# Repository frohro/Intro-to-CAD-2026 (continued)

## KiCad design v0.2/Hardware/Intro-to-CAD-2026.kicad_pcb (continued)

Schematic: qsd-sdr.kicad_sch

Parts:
C1, C20, C23, C30, C31, C32, C52, C81: 100nF; C_0805; Voltage Rated 100V; Tolerance ±10%; Part CL21B104KCFNNNE; LCSC C28233
C14, C16, C19, C22: 10nF; C_0603; Voltage Rated 50V; Tolerance ±5%; LCSC C1664
C18, C28, C93, C94: 330pF; C_0603; Voltage Rated 50V; Tolerance ±5%; Part CL10C331JB8NNNC; LCSC C1664
C21, C29: 1uF; C_0805; Voltage Rated 50V; Tolerance ±10%; Part CL21B105KBFNNNE; LCSC C28323
C33: 10uF; C_1206; Voltage Rated 50V; Tolerance ±10%; Part CL31A106KBHNNNE; LCSC C13585
C82, C83: 100uF; C_CASE-B-3528-21(mm); Tolerance ±10%; Rated Voltage 6.3V; Part TAJB107K006RNJ; LCSC C16133
FB3: FB_0805; Current Rating 500mA; Tolerance ±25%; Part GZ2012D601TF; LCSC C1017
J11: SDR ANT; Conn_Coaxial_Frohne; not fitted
J12: SDR Out; Jack_3.5mm_CUI_SJ-3523-SMT_Horizontal; LCSC C18594
JP1: Turns; SolderJumper-2_P1.3mm_Bridged2Bar_RoundedPad1.0x1.5mm
JP9, JP10: 330pf; SolderJumper-2_P1.3mm_Bridged_RoundedPad1.0x1.5mm
JP86: Filter; SolderJumper-2_P1.3mm_Bridged2Bar_RoundedPad1.0x1.5mm
JP88, JP89: GND_LP_SND; SolderJumper-2_P1.3mm_Open_RoundedPad1.0x1.5mm
Je3: Filter; PinHeader_1x04_P2.54mm_Vertical; LCSC C2718488; not fitted
R1, R4: 10kΩ; R_0805; Overload Voltage (Max) 150V; Tolerance ±1%; Part 0805W8F1002T5E; LCSC C17414
R8, R9: 47Ω; R_0805; Overload Voltage (Max) 150V; Tolerance ±1%; Part 0805W8F470JT5E; LCSC C17714
R11: 1Ω; R_0805; Overload Voltage (Max) 150V; Tolerance ±1%; Part 0805W8F100KT5E; LCSC C25271
R12, R13: 1.5kΩ; R_0402; Overload Voltage (Max) 50V; Tolerance ±1%; Part 0402WGF1501TCE; LCSC C25867
R30: 10Ω; R_0603; Overload Voltage (Max) 75V; Tolerance ±1%; Part 0603WAF100JT5E; LCSC C22859
R58, R59, R60, R61: 10Ω; R_0402; Overload Voltage (Max) 50V; Tolerance ±1%; Part 0402WGF100JTCE; LCSC C25077
TP6: 180; TestPoint_THTPad_D2.0mm_Drill1.0mm
TP7: 270; TestPoint_THTPad_D2.0mm_Drill1.0mm
TP10, TP12: GND; TestPoint_THTPad_D2.0mm_Drill1.0mm
TP11: VA/2; TestPoint_THTPad_D2.0mm_Drill1.0mm
TP14: 0; TestPoint_THTPad_D2.0mm_Drill1.0mm
TP16: 90; TestPoint_THTPad_D2.0mm_Drill1.0mm
TP17: I; TestPoint_THTPad_D2.0mm_Drill1.0mm
TP18: Q; TestPoint_THTPad_D2.0mm_Drill1.0mm
TR1: H1102NLT; XFMR_H1102NLT; LCSC C20623173
U5, U8: OPA1612AxD; SOIC-8_3.9x4.9mm_P1.27mm; LCSC C94590
U7: SN74CBT3253DBQR; DBQ0016A-IPC_A; LCSC C2674552
e5: Groundloop_Insurance; SolderJumper-2_P1.3mm_Bridged_RoundedPad1.0x1.5mm

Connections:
/I: C29.2, J12.R; also elsewhere on the board
/I_CLK: U7.14 (S0); also elsewhere on the board
/Q: C21.1, J12.T; also elsewhere on the board
/Q_CLK: U7.2 (S1); also elsewhere on the board
GND: C14.2, C16.2, C19.2, C20.1, C22.2, C23.1, C30.1, C31.1, C32.1, C33.2, C52.1, C82.2, JP89.1 (A), R4.1, R30.2, TP10.1 (1_1), TP12.1 (1_1), U5.4 (V-), U7.1 (1~OE), U7.8 (GND), U7.15 (2~OE), U8.4 (V-), e5.1 (A); also elsewhere on the board
unnamed: C33.1, R11.2
unnamed: J11.2 (Ext), JP1.1 (A), JP88.1 (A), JP89.2 (B), Je3.2, Je3.3
unnamed: C1.1, J11.1 (In)
unnamed: JP1.2 (B), TR1.7 (C_RD)
unnamed: C18.2, C29.1, JP9.1 (A), R12.2, TP17.1 (1_1), U8.7
unnamed: C93.2, JP9.2 (B)
unnamed: C94.2, JP10.1 (A)
unnamed: C21.2, C28.2, JP10.2 (B), R13.2, TP18.1 (1_1), U8.1
unnamed: C1.2, JP86.1 (A), Je3.1
unnamed: JP86.2 (B), Je3.4, TR1.8 (RD-)
unnamed: JP88.2 (B), TR1.6 (RD+)
unnamed: C20.2, C81.1, C82.1, C83.2, R1.1, R4.2, TP11.1 (1_1), TR1.10 (C_RX)
unnamed: TR1.11 (RX+), U7.9 (2A)
unnamed: TR1.9 (RX-), U7.7 (1A)
unnamed: R61.2, U5.3 (+)
unnamed: R8.1, U5.1, U5.2 (-)
unnamed: R58.2, U5.5 (+)
unnamed: R9.1, U5.6 (-), U5.7
unnamed: C16.1, R60.1, TP14.1 (1_1), U7.6 (1B1), U7.13 (2B4)
unnamed: C14.1, R59.1, TP16.1 (1_1), U7.5 (1B2), U7.12 (2B3)
unnamed: C22.1, R58.1, TP7.1 (1_1), U7.4 (1B3), U7.11 (2B2)
unnamed: C19.1, R61.1, TP6.1 (1_1), U7.3 (1B4), U7.10 (2B1)
unnamed: C23.2, FB3.1, U7.16 (VCC)
unnamed: R59.2, U8.3 (+)
unnamed: C28.1, C94.1, R9.2, R13.1, U8.2 (-)
unnamed: R60.2, U8.5 (+)
unnamed: C18.1, C93.1, R8.2, R12.1, U8.6 (-)
unnamed: C52.2, J12.S, R30.1, e5.2 (B)
VDDA: C30.2, C31.2, C32.2, C81.2, C83.1, FB3.2, R1.2, R11.1, U5.8 (V+), U8.8 (V+); also elsewhere on the board

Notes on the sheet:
We should switch X this transformer so the choke is on the input.
Mixer 1 or 2
Op amps picked for low noise, +/- 2.25 V supply, being in the same package, and only $1 for the package.
External Filter Option
Double check to see we corrected v0.1 mixer error....
The image rejection is vastly superior with all four mixer outputs used. See the simulations. I like the symmetry. The buffer is needed to isolate the inverting sampling capacitors.
Mixer
Scope GND connections
Amplifier/Filter

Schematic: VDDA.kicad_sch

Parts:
C2, C5, C35, C41, C42, C85, C88: 10uF; C_1206; Voltage Rated 50V; Tolerance ±10%; Part CL31A106KBHNNNE; LCSC C13585
C17, C36, C37, C89, C90: 100uF; C_CASE-B-3528-21(mm); Tolerance ±10%; Rated Voltage 6.3V; Part TAJB107K006RNJ; LCSC C16133
C40, C87: 4.7pF; C_0603; Voltage Rated 50V; Part 0603CG4R7C500NT; LCSC C1669
C43, C55, C86: 0.1u; C_0805_2012Metric; LCSC C49678
D1, D2, D3: SS14; D_SMA; Forward Voltage (Vf@If) 550mV@1A; Reverse Voltage (Vr) 40V; Part SS14; LCSC C2480
FB2: FB_0805; Current Rating 500mA; Tolerance ±25%; Part GZ2012D601TF; LCSC C1017
FB5, FB6, FB8, FB9: FB_0805; Current Rating 800mA; Tolerance ±25%; Part GZ2012D101TF; LCSC C1015
J5: Conn_01x02; PinHeader_1x02_P2.54mm_Vertical; not fitted
JP2: +0.3V; SolderJumper-2_P1.3mm_Open_RoundedPad1.0x1.5mm
Q1: AO3401A; Q_SOT-23; Part AO3401A; LCSC C15127
R5: 33kΩ; R_0805; Overload Voltage (Max) 150V; Tolerance ±1%; Part 0805W8F3302T5E; LCSC C17633
R6: 12kΩ; R_0805; Overload Voltage (Max) 150V; Tolerance ±1%; Part 0805W8F1202T5E; LCSC C17444
R7, R20, R21, R25, R73: 1Ω; R_0805; Overload Voltage (Max) 150V; Tolerance ±1%; Part 0805W8F100KT5E; LCSC C25271
R10: 27kΩ; R_0805; Overload Voltage (Max) 150V; Tolerance ±1%; Part 0805W8F2702T5E; LCSC C17593
R24: 47kΩ; R_0805; Overload Voltage (Max) 150V; Tolerance ±1%; Part 0805W8F4702T5E; LCSC C17713
R28: 100kΩ; R_0805; Overload Voltage (Max) 150V; Tolerance ±1%; Part 0805W8F1003T5E; LCSC C149504
TP25: +5; TestPoint_THTPad_D2.0mm_Drill1.0mm
TP26: VDDA; TestPoint_THTPad_D2.0mm_Drill1.0mm
TP27: 3.3V_A; TestPoint_THTPad_D2.0mm_Drill1.0mm
U6: L78M05ABDT-TR; TO-252-2_L6.5-W6.1-P4.58-LS10.0-TL; Output Voltage 5V; Part L78M05ABDT-TR; LCSC C58069
e1, e10: SGM2205-ADJXTDB8G/TR; DFN-8-1EP_3x3mm_P0.65mm_EP1.55x2.4mm; LCSC C5152847

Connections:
+3.3VA: C89.1, C90.1, FB9.2, TP27.1 (1_1); also elsewhere on the board
+4.7V: C2.1, D3.1, JP2.2 (B), Q1.3 (D), TP25.1 (1_1); also elsewhere on the board
GND: C2.2, C5.2, C17.2, C35.2, C36.2, C37.2, C41.2, C42.2, C43.2, C55.2, C85.2, C86.2, C88.2, C89.2, C90.2, J5.1, R6.2, R10.2, R28.2, U6.4 (GND), e1.7 (GND), e1.9 (PAD), e10.7 (GND), e10.9 (PAD); also elsewhere on the board
unnamed: C35.1, C40.1, R5.2, R7.1, R20.1, e1.3 (VOUT), e1.4 (VOUT)
unnamed: C42.1, D1.2, R21.1
unnamed: C87.1, C88.1, R24.2, R25.1, R73.1, e10.3 (VOUT), e10.4 (VOUT)
unnamed: D1.1, FB2.2
unnamed: FB5.1, R7.2, R20.2
unnamed: FB9.1, R25.2, R73.2
unnamed: D2.2, J5.2
unnamed: C43.1, D3.2, JP2.1 (A), U6.3 (VOUT)
unnamed: C41.1, D2.1, Q1.1 (G), R21.2, R28.1, U6.1 (VIN)
unnamed: FB2.1, FB6.1, FB8.1, Q1.2 (S)
unnamed: C5.1, C55.1, FB6.2, e1.1 (VIN), e1.2 (VIN), e1.8 (EN)
unnamed: C40.2, R5.1, R6.1, e1.6 (SENSE/ADJ)
unnamed: C85.1, C86.1, FB8.2, e10.1 (VIN), e10.2 (VIN), e10.8 (EN)
unnamed: C87.2, R10.1, R24.1, e10.6 (SENSE/ADJ)
VDDA: C17.1, C36.1, C37.1, FB5.2, TP26.1 (1_1); also elsewhere on the board

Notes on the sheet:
VDDA Regulator
We are running VDDA at 4.5V (minimum allowed).
Clean analog supply (+5 to +15 V)
This powers the Pico when we are not using USB.
This connection goes to VSYS (pico) or Vin (YD-RP2040).

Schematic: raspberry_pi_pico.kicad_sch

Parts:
C39: 10uF; C_CASE-A-3216-18(mm); Tolerance ±10%; Rated Voltage 16V; Part TAJA106K016RNJ; LCSC C7171
J2: Conn_02x20_Counter_Clockwise; PinSocket_2x20_P2.54mm_Vertical_pins1-20; LCSC C2977589
J3: Conn_02x20_Counter_Clockwise; PinSocket_2x20_P2.54mm_Vertical_Counterclockwise_pins21-40; LCSC C2977589
J4: Conn_01x20_Socket; PinSocket_1x20_P2.54mm_Vertical; LCSC C2905423
J7: Conn_01x01_Pin; PinHeader_1x01_P2.54mm_Vertical; not fitted
J10: Conn_01x20_Socket; PinSocket_1x20_P2.54mm_Vertical-pins21-40; LCSC C2905423
JP20, JP21, JP22, JP23, JP24, JP25, JP26, JP27, JP28, JP29, JP30, JP31, JP32, JP33, JP34, JP35, JP36, JP37, JP38, JP39, JP40, JP41, JP42, JP43, JP44, JP45, JP46, JP47, JP48, JP49, JP51, JP52, JP53, JP54, JP55, JP56, JP57, JP58, JP59, JP60, JP61, JP62, JP63, JP64, JP65, JP66, JP67, JP68, JP70, JP71, JP72, JP73, JP74, JP75, JP76, JP77, JP78, JP79, JP80, JP81, JP82, JP83: Jumper_2_Bridged; SolderJumper-2_P1.3mm_Bridged2Bar_RoundedPad1.0x1.5mm
JP50: USB_ONLY; SolderJumper-2_P1.3mm_Bridged2Bar_RoundedPad1.0x1.5mm
R29: 20kΩ; R_0805; Overload Voltage (Max) 150V; Tolerance ±1%; Part 0805W8F2002T5E; LCSC C4328
S1: Tactile Button, 160gf; SW_TS-1088-AR02016; Voltage Rating (Dc) 12V; Part TS-1088-AR02016; LCSC C720477
U3: Pico; RPi_Pico_SMD_TH; not fitted

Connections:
+3.3V: C39.1, J2.3 (Pin_38), J3.30, JP23.1 (A), R29.1; also elsewhere on the board
+4.7V: JP20.1 (A), JP21.1 (A), JP35.2 (B), JP50.1 (A); also elsewhere on the board
/ANG_A: JP29.1 (A); also elsewhere on the board
/ANG_B: JP30.1 (A); also elsewhere on the board
/BCK: JP78.2 (B); also elsewhere on the board
/BCK2: JP75.2 (B); also elsewhere on the board
/BTN: JP82.2 (B); also elsewhere on the board
/CS: JP68.2 (B); also elsewhere on the board
/DATA: JP77.2 (B); also elsewhere on the board
/ECHO: JP27.1 (A); also elsewhere on the board
/INA: JP26.1 (A); also elsewhere on the board
/INB: JP25.1 (A); also elsewhere on the board
/LRCK: JP33.1 (A); also elsewhere on the board
/MISO: JP67.2 (B); also elsewhere on the board
/MOSI: JP71.2 (B); also elsewhere on the board
/OSC_SCL: JP81.2 (B); also elsewhere on the board
/OSC_SDA: JP80.2 (B); also elsewhere on the board
/PICO_MCLK: JP83.2 (B); also elsewhere on the board
/RGB_DIN: JP31.1 (A); also elsewhere on the board
/Raspberry_Pi_Pico/3V3_EN: JP22.1 (A)
/Raspberry_Pi_Pico/ADC_VREF: JP24.1 (A)
/Raspberry_Pi_Pico/RST: J10.30 (Pin_11), R29.2, S1.1 (A), U3.30 (RUN)
/SCLK: JP34.1 (A); also elsewhere on the board
/SD2: JP74.2 (B); also elsewhere on the board
/SDIN: JP32.1 (A); also elsewhere on the board
/SD_CD: JP72.2 (B); also elsewhere on the board
/SPI_CK: JP70.2 (B); also elsewhere on the board
/SW_C: JP73.2 (B); also elsewhere on the board
/TRIG: JP28.1 (A); also elsewhere on the board
/WS: JP79.2 (B); also elsewhere on the board
/WS2: JP76.2 (B); also elsewhere on the board
GND: C39.2, J2.8, J2.13, J2.18, J3.23, J3.28, J3.33 (Pin_8), J3.38 (Pin_3), J4.3, J4.8, J4.13, J4.18, J10.23 (Pin_18), J10.28 (Pin_13), J10.33 (Pin_8), J10.38 (Pin_3), S1.2 (B), U3.3 (GND), U3.8 (GND), U3.13 (GND), U3.18 (GND), U3.23 (GND), U3.28 (GND), U3.33 (AGND), U3.38 (GND); also elsewhere on the board
unnamed: J2.1, JP51.2 (B), JP67.1 (A)
unnamed: J2.2, JP52.2 (B), JP68.1 (A)
unnamed: J2.10, JP58.2 (B), JP75.1 (A)
unnamed: J2.11, JP59.2 (B), JP76.1 (A)
unnamed: J2.12, JP60.2 (B), JP77.1 (A)
unnamed: J2.14, JP61.2 (B), JP78.1 (A)
unnamed: J2.15, JP62.2 (B), JP79.1 (A)
unnamed: J2.16, JP63.2 (B), JP80.1 (A)
unnamed: J2.17, JP64.2 (B), JP81.1 (A)
unnamed: J2.19, JP65.2 (B), JP82.1 (A)
unnamed: J2.20, JP66.2 (B), JP83.1 (A)
unnamed: J2.9, JP57.2 (B), JP74.1 (A)
unnamed: J2.7, JP56.2 (B), JP73.1 (A)
unnamed: J2.6, JP55.2 (B), JP72.1 (A)
unnamed: J2.5, JP54.2 (B), JP71.1 (A)
unnamed: J2.4, JP53.2 (B), JP70.1 (A)
unnamed: J3.40 (Pin_1), JP20.2 (B), JP35.1 (A)
unnamed: J3.39 (Pin_2), JP21.2 (B), JP36.1 (A)
unnamed: J3.31 (Pin_10), JP27.2 (B), JP42.1 (A)
unnamed: J3.29 (Pin_12), JP28.2 (B), JP43.1 (A)
unnamed: J3.27 (Pin_14), JP29.2 (B), JP44.1 (A)
unnamed: J3.26 (Pin_15), JP30.2 (B), JP45.1 (A)
unnamed: J3.25 (Pin_16), JP31.2 (B), JP46.1 (A)
unnamed: J3.24 (Pin_17), JP32.2 (B), JP47.1 (A)
unnamed: J3.22 (Pin_19), JP33.2 (B), JP48.1 (A)
unnamed: J3.21 (Pin_20), JP34.2 (B), JP49.1 (A)
unnamed: J3.32 (Pin_9), JP26.2 (B), JP41.1 (A)
unnamed: J3.34 (Pin_7), JP25.2 (B), JP40.1 (A)
unnamed: J3.35 (Pin_6), JP24.2 (B), JP39.1 (A)
unnamed: J3.36 (Pin_5), JP23.2 (B), JP38.1 (A)
unnamed: J3.37 (Pin_4), JP22.2 (B), JP37.1 (A)
unnamed: J4.1, JP51.1 (A), U3.1 (GPIO0)
unnamed: J4.2, JP52.1 (A), U3.2 (GPIO1)
unnamed: J4.4, JP53.1 (A), U3.4 (GPIO2)
unnamed: J4.5, JP54.1 (A), U3.5 (GPIO3)
unnamed: J4.6, JP55.1 (A), U3.6 (GPIO4)
unnamed: J4.7, JP56.1 (A), U3.7 (GPIO5)
unnamed: J4.9, JP57.1 (A), U3.9 (GPIO6)
unnamed: J4.10, JP58.1 (A), U3.10 (GPIO7)
unnamed: J4.11, JP59.1 (A), U3.11 (GPIO8)
unnamed: J4.12, JP60.1 (A), U3.12 (GPIO9)
unnamed: J4.14, JP61.1 (A), U3.14 (GPIO10)
unnamed: J4.15, JP62.1 (A), U3.15 (GPIO11)
unnamed: J4.16, JP63.1 (A), U3.16 (GPIO12)
unnamed: J4.17, JP64.1 (A), U3.17 (GPIO13)
unnamed: J4.19, JP65.1 (A), U3.19 (GPIO14)
unnamed: J4.20, JP66.1 (A), U3.20 (GPIO15)
unnamed: J7.1 (Pin_1_1), J10.40 (Pin_1), JP50.2 (B), U3.40 (VBUS)
unnamed: J10.39 (Pin_2), JP36.2 (B), U3.39 (VSYS)
unnamed: J10.37 (Pin_4), JP37.2 (B), U3.37 (3V3_EN)
unnamed: J10.36 (Pin_5), JP38.2 (B), U3.36 (3V3)
unnamed: J10.35 (Pin_6), JP39.2 (B), U3.35 (ADC_VREF)
unnamed: J10.34 (Pin_7), JP40.2 (B), U3.34 (GPIO28_ADC2)
unnamed: J10.32 (Pin_9), JP41.2 (B), U3.32 (GPIO27_ADC1)
unnamed: J10.31 (Pin_10), JP42.2 (B), U3.31 (GPIO26_ADC0)
unnamed: J10.29 (Pin_12), JP43.2 (B), U3.29 (GPIO22)
unnamed: J10.27 (Pin_14), JP44.2 (B), U3.27 (GPIO21)
unnamed: J10.26 (Pin_15), JP45.2 (B), U3.26 (GPIO20)
unnamed: J10.25 (Pin_16), JP46.2 (B), U3.25 (GPIO19)
unnamed: J10.24 (Pin_17), JP47.2 (B), U3.24 (GPIO18)
unnamed: J10.22 (Pin_19), JP48.2 (B), U3.22 (GPIO17)
unnamed: J10.21 (Pin_20), JP49.2 (B), U3.21 (GPIO16)

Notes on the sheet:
J2 and J3 allow you to connect Dupont connectors to other external modules.
Students can connect their modules to GPIO7-22.
RST here is redundant if using a YD-RP2040.
V+ (YD-RP2040) VBUS (Pico)
If you are using a real Pico, this jumper bridges a Schottky diode from USB in to Vsys (4.7v with it open, 5.0v from USB port with it soldered)
These jumpers are for changing GPIO pins if necessary. They also allow you to connect modules similar to a breadboard.
For the YD-RP2040 we want the USB Only jumper shorted.
Renumber the footprint pin numbers for J2, J3 and J4.

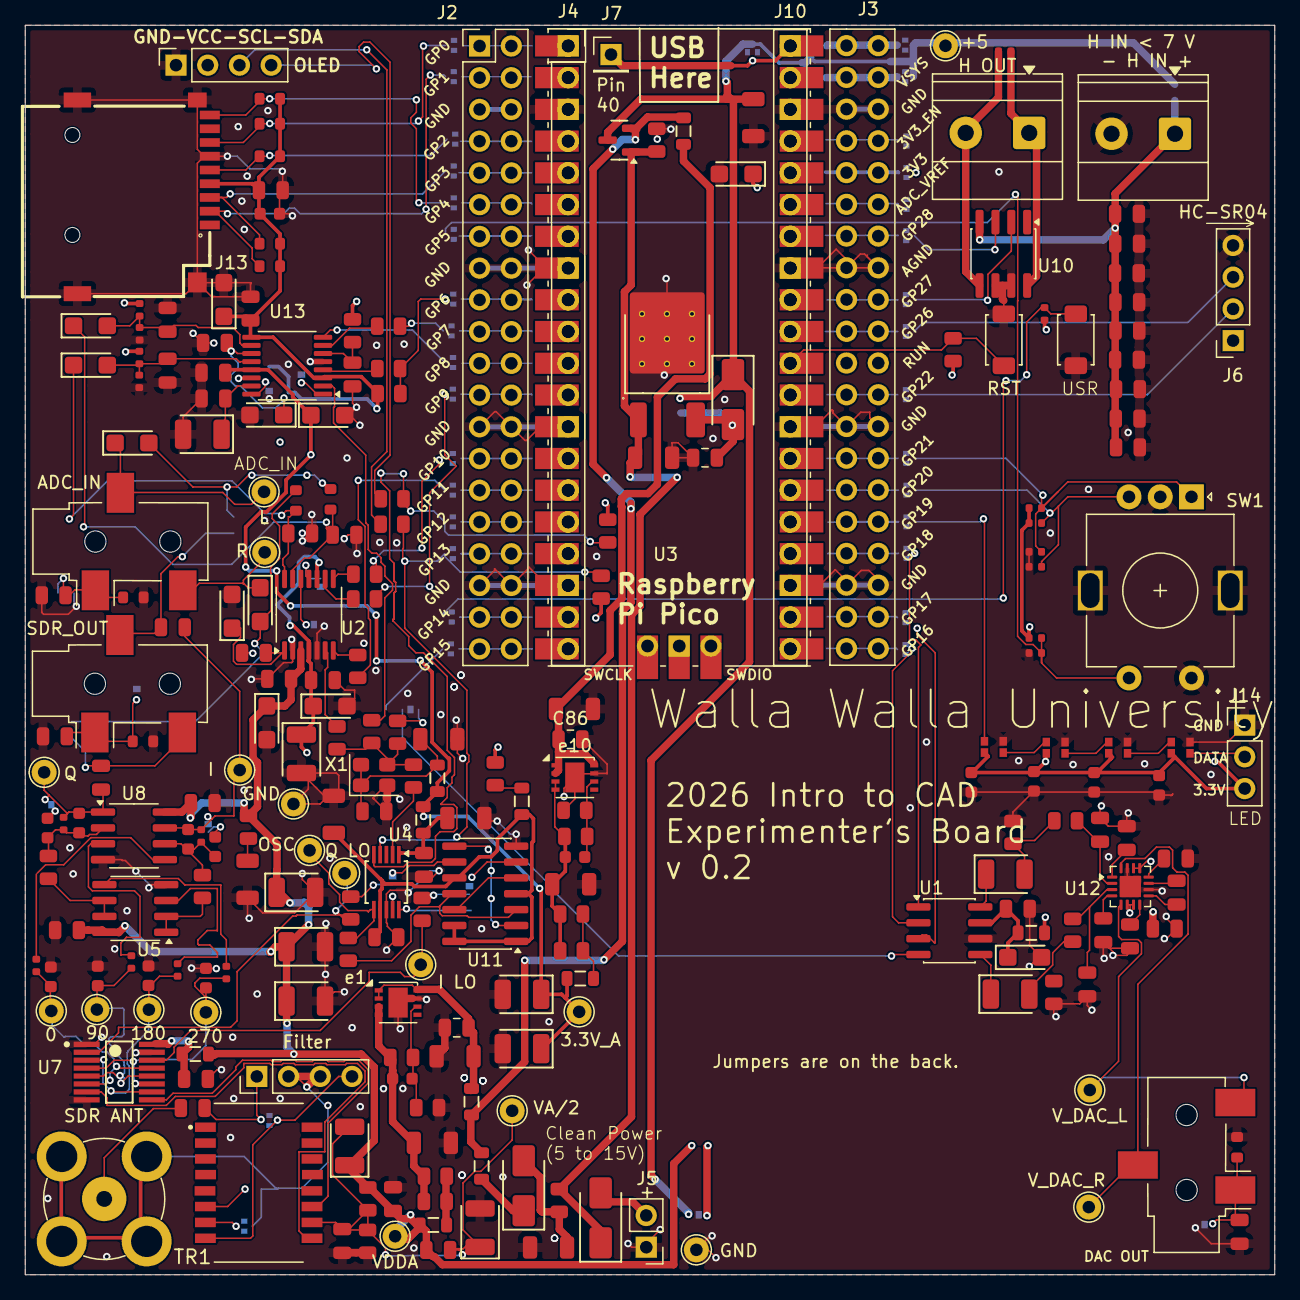
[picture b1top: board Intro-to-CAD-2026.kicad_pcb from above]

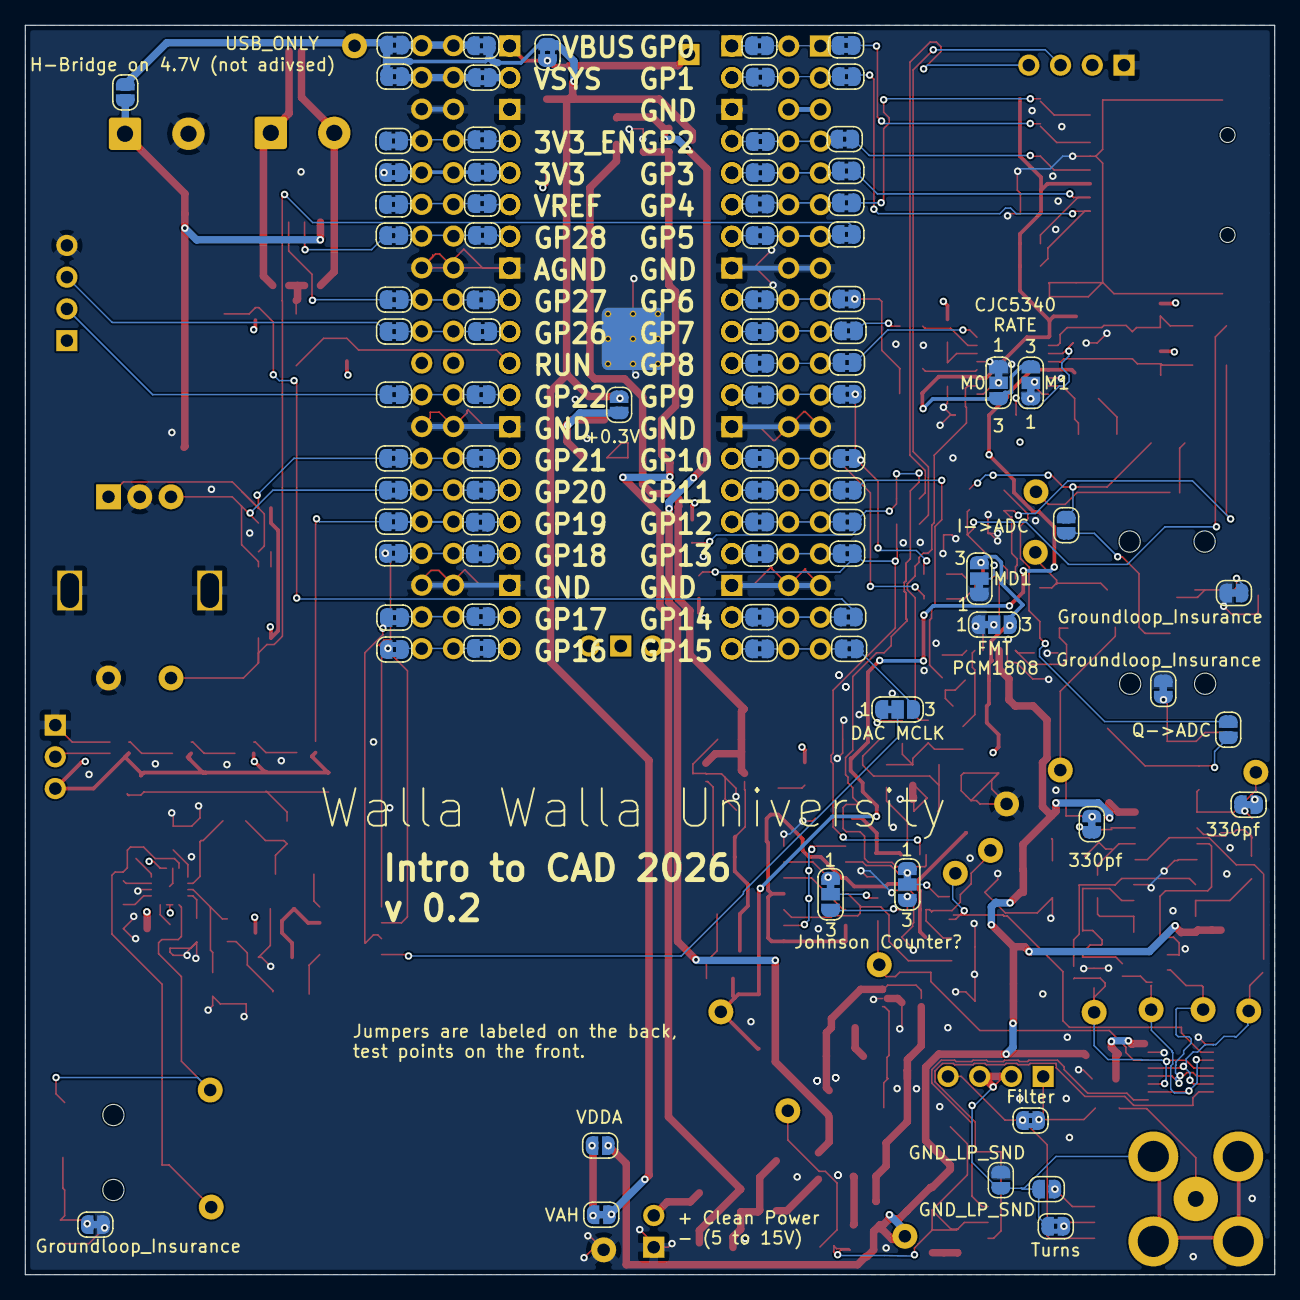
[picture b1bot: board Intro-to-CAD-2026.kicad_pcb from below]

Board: 4 copper layers, 100.0 x 100.0 mm, 323 parts (85 on the bottom side), 208 nets.

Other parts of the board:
C68, C69, C70, C71: 100nF; C_0603
D8, D9, D10, D11: XL-0807RGBC-2812B; C3646929e
J14: Conn_01x03; PinHeader_1x03_P2.54mm_Vertical

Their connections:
+3.3V: C68.2, C69.2, C70.2, C71.2, D8.4 (VDD), D9.4 (VDD), D10.4 (VDD), D11.4 (VDD), J14.3; also elsewhere on the board
/RGB_DIN: D8.3 (DIN); also elsewhere on the board
GND: C68.1, C69.1, C70.1, C71.1, D8.2 (GND), D9.2 (GND), D10.2 (GND), D11.2 (GND), J14.1; also elsewhere on the board
unnamed: D8.1 (DOUT), D9.3 (DIN)
unnamed: D9.1 (DOUT), D10.3 (DIN)
unnamed: D10.1 (DOUT), D11.3 (DIN)
unnamed: D11.1 (DOUT), J14.2

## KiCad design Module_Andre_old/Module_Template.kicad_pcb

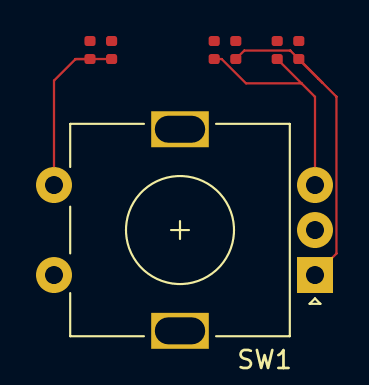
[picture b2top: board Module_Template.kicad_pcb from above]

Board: 4 copper layers, 7 parts (0 on the bottom side), 5 nets.

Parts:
C1: 100nF; C_0402
C2, C3: 10nF; C_0402
R1, R2, R3: 10kΩ; R_0402
SW1: RotaryEncoder_Switch_MP; RotaryEncoder_Alps_EC11E-Switch_Vertical_H20mm

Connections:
+3V3: R1.1, R2.1, R3.1
/GPIO_A: C2.1, R2.2, SW1.A
/GPIO_B: C3.1, R3.2, SW1.B
/GPIO_C: C1.1, R1.2, SW1.S1
GND: C1.2, C2.2, C3.2, SW1.C, SW1.MP, SW1.S2

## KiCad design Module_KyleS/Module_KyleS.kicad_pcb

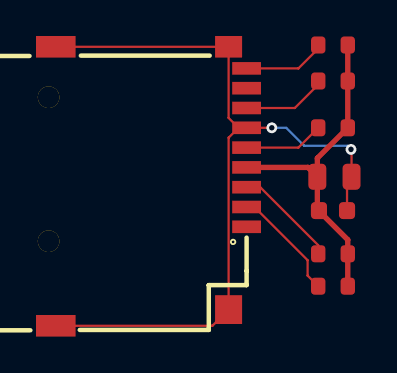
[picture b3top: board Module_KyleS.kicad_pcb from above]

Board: 4 copper layers, 8 parts (0 on the bottom side), 7 nets.

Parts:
C1: 10uF; C_0805
C2: 100nF; C_0603
J1: Micro_SD-TF_PUSH; TF-SMD_TF-PUSH
R1, R2, R3, R4, R5: 10kΩ; R_0603

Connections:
+3.3V: C1.1, C2.1, J1.4 (VDD), R1.2, R2.2, R3.1, R4.1, R5.2
/CS: J1.2 (DAT3/CS), R4.2
/MISO: J1.7 (DAT0/SO), R3.2
/MOSI: J1.3 (CMD/SI), R2.1
/SD_CD: J1.CD (DET), R5.1
/SPI_CK: J1.5 (CLK), R1.1
GND: C1.2, C2.2, J1.6 (VSS), J1.10 (SHIELD), J1.11 (SHIELD), J1.12 (SHIELD), J1.13 (SHIELD)

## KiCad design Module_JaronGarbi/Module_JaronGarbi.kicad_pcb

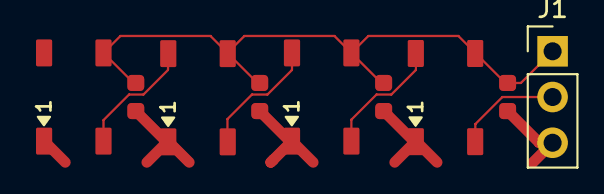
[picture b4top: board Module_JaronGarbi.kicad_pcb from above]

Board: 4 copper layers, 9 parts (0 on the bottom side), 6 nets.

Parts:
C1, C2, C3, C4: 100nF; C_0603
D1, D2, D3, D4: WS2812B; LED_WS2812B_PLCC4_5.0x5.0mm_P3.2mm
J1: Conn_01x03; PinHeader_1x03_P2.54mm_Vertical

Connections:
+3.3V: C1.2, C2.2, C3.2, C4.2, D1.1 (VDD), D2.1 (VDD), D3.1 (VDD), D4.1 (VDD), J1.3
GND: C1.1, C2.1, C3.1, C4.1, D1.3 (VSS), D2.3 (VSS), D3.3 (VSS), D4.3 (VSS), J1.1
unnamed: D1.2 (DOUT), D2.4 (DIN)
unnamed: D2.2 (DOUT), D3.4 (DIN)
unnamed: D3.2 (DOUT), D4.4 (DIN)
unnamed: D4.2 (DOUT), J1.2

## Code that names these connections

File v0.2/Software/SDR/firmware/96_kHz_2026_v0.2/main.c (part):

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 *   export PICO_TINYUSB_PATH=$HOME/tinyusb
 *
 * Pin assignments (Intro-to-CAD-2026 v0.2 board, YD-RP2040 module):
 *   GPIO6   FMT  -- PCM1808 FMT (OUT, LOW = I2S standard format)
 *   GPIO8   MD1  -- PCM1808 MD1 (IN, HIGH=256fs/96kHz, LOW=512fs/48kHz)
 *   GPIO12  SDA  -- Si5351a I2C data
 *   GPIO13  SCL  -- Si5351a I2C clock
 *   GPIO9   DATA -- PCM1808 DOUT (PIO in_base)
 *   GPIO10  BCK  -- PCM1808 BCK  (PIO in_base + 1)
 *   GPIO11  WS   -- PCM1808 LRCK (PIO in_base + 2)
 *   GPIO22  DBG  -- DMA ISR toggle (logic analyser probe, ~500 Hz square wave)
 *
 * Protocol (line-oriented ASCII -- matches quisk_conf_96k.py):
 *
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#include "si5351.h"

/* ---- GPIO pin assignments ----------------------------------------- */
#define FMT_PIN       6    /* PCM1808 FMT   -> LOW = I2S standard fmt   */
#define MD1_PIN       8    /* PCM1808 MD1   -> LOW = Master 512fs       */
#define I2C_SDA_PIN   12   /* Si5351a SDA */
#define I2C_SCL_PIN   13   /* Si5351a SCL */
#define DATA_PIN      9    /* PCM1808 DOUT  -> PIO in_base */
#define BCK_PIN       10   /* PCM1808 BCK   -> PIO in_base + 1 */
#define WS_PIN        11   /* PCM1808 LRCK  -> PIO in_base + 2 */
#define DEBUG_PIN     22   /* DMA ISR toggle for logic analyser */

/* 100 kHz: required for the MS5351M clone on the 2026 v0.1 board.
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    gpio_put(DEBUG_PIN, 0);

    /* PCM1808 FMT=LOW -> I2S standard format (MSB delayed 1 BCK from WS) */
    gpio_init(FMT_PIN);
    gpio_set_dir(FMT_PIN, GPIO_OUT);
    gpio_put(FMT_PIN, 0);

    /* PCM1808 MD1=HIGH + MD0 tied HIGH on board -> Master 256fs mode.
     * BCK = 64 x 96000 = 6.144 MHz, LRCK = 96 kHz, SCKI = 24.576 MHz. */
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
    pio_sm_config c = i2s_rx_program_get_default_config(g_pio_offset);

    /* PCM1808 outputs DATA (GPIO14), BCK (GPIO15), WS (GPIO16).
     * Set these pins to PIO function and input direction across the range.
     * We enable pull-ups to prevent the I/O error if the PCM1808 is missing. */
    for (int pin = DATA_PIN; pin <= WS_PIN; pin++) {
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    }
    pio_sm_set_consecutive_pindirs(pio, sm, DATA_PIN, 3, false);

    /* in_base = GPIO14; BCK is offset 1, WS is offset 2 */
    sm_config_set_in_pins(&c, DATA_PIN);

    /* Shift LEFT (MSB first), autopush at 32 bits -- one word per channel */
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
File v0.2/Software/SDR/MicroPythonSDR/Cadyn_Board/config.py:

# Board configuration for MicroPythonSDR
#
# Change BOARD to match the hardware you are deploying to, then copy all
# .py files in this directory to the root of the Pico's filesystem.
#
# Supported boards
# ----------------
#   "INTRO_CAD_2026"  —  Intro-to-CAD-2026 SDR board (CPTR-480 class board)
#   "CADYN_PICO_SDR"  —  Cadyn's hand-wired Pico SDR (reference build)

BOARD = "CADYN_PICO_SDR"

# -----------------------------------------------------------------------
if BOARD == "INTRO_CAD_2026":
    # I2C bus 0: GPIO12 = SDA, GPIO13 = SCL  (RP2040 I2C0 alternate mapping)
    SDA_PIN      = 12
    SCL_PIN      = 13
    # MS5351M internal oscillator frequency.
    # Update this value after calibrating against a known-frequency signal
    # (e.g., WWV at 10 MHz, or a calibrated signal generator).
    CRYSTAL_FREQ = 24_576_000.0
    DEFAULT_FREQ = 7_074_000      # FT8 on 40 m
    LED_PIN      = 23             # WS2812B NeoPixel on YD-RP2040 V1.3

# -----------------------------------------------------------------------
elif BOARD == "CADYN_PICO_SDR":
    # I2C bus 0: GPIO4 = SDA, GPIO5 = SCL  (RP2040 I2C0 default mapping)
    SDA_PIN      = 4
    SCL_PIN      = 5
    # Calibrated crystal value from Cadyn's unit.
    CRYSTAL_FREQ = 25_000_700.02
    DEFAULT_FREQ = 7_000_000
    LED_PIN      = None           # no NeoPixel on this build

# -----------------------------------------------------------------------
else:
    raise ValueError("Unknown BOARD: " + BOARD)

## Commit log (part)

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2026-01-30 Cleaned up unwanted folders.
2026-01-30 Cleaning up unneeded files...
2026-01-30 More move fixes...
2026-01-31 Placed more parts
    Still need to fix errors in schematic...
2026-01-31 Fixed a few schematic errors.
2026-02-01 More edits...
2026-02-02 Fixed a few more things and started routing.
2026-02-02 Added R37 asd R38
2026-02-02 More tuning.
2026-02-03 Added some power traces
2026-02-03 Routing everything now.
2026-02-03 Unconnected 29
2026-02-03 Unconnected 16
2026-02-03 0 Unconnected 53 Errors
2026-02-03 0 unconnected, 0 Errors 411+ warnings
2026-02-04 Checking costs at JLCPCB
2026-02-06 328 warnings
2026-02-06 No warnings, errors
2026-02-06 Added som e3D models...
2026-02-08 Moved my work to the main directory.
2026-02-11 Ignore production *.zip
2026-02-11 Fixed offset on Pico 3D view
2026-02-11 Ignored overlaps, etc.
    Ignored a bunch of stuff that doesn't matter. I checked these earlier.
2026-02-12 An edit for Paola and Shaina
2026-02-12 Eliminated 4 resistors.
2026-02-13 saved and updated.
2026-02-13 Changed C_sample to 10nf
    And added 10 Ohm damping resistors.
2026-02-15 Changed R55-58 values.
2026-02-18 LTspice files updated
2026-02-18 Added audio amplifier
2026-02-19 Moved DAC jack and planes.
2026-02-19 Save to go home.
2026-02-19 Added module schematics.
2026-02-19 Imported Student Parts
    Not using Project Instances yet.
2026-02-19 Modules iimporoted but not wired.
2026-02-19 Going to school.
2026-02-19 No Errors No Warnings
    Some were excluded.
2026-02-20 Beautifying it.
2026-02-20 Adding TC118S
2026-02-20 Added H-Bridge PCB Edits
2026-02-20 Getting JLCPCB Price
2026-02-20 Replaced Jaron's LEDs
    They were only for Standard Boards.
2026-02-20 Four layer now going to six (this is still 4)
2026-02-20 Editing 6 layer
2026-02-22 Fixed DAC
2026-02-22 Found and replaced 10 buried/blind vias.
2026-02-22 Fixed RST
2026-02-22 Fixed 3.5mm jack labels
2026-02-22 More labels
2026-02-22 Warning on OLED
2026-02-22 SW1 Rotated.
2026-02-22 text tweaks
2026-02-22 Submitted.
2026-02-24 Fixed U7 to the right part (C2674552)
2026-02-24 Finished fix of U7.
2026-02-24 One more change on U7.
2026-02-24 Fixed pinout error on LEDs.
2026-02-25 Added *lck to .gitignore
2026-02-25 Resubmitting to JLCPCB
2026-02-25 Beautify schematic
2026-02-25 Add .gbr to .gitignore
2026-02-26 Wrong Footprint for U7
2026-02-26 Ready for submission?
2026-02-26 Submission?
2026-02-27 Changed for Resubmission 2-27-2026
2026-03-01 Added Gerbers to .gitignore and kept production.
2026-03-01 Fixed label on DAC schematic.
2026-04-01 Initial v0.2
    Fixed SCL-SDA swap, 3V3 on encoder, and 3D models for Kicad 10
2026-04-02 Added the QSD SDR Circuit Summary
2026-04-14 Updated errors
2026-04-24 Starting a new branch for v0.2
2026-04-24 Addid intital pcb commits
2026-04-27 Added noise simulation
2026-04-30 Add board-specific MicroPython SDR firmware and Quisk configs
2026-04-30 Fix Cadyn Quisk crystal fallback
2026-05-04 Adding fixes:
    LDO for LO. Reduce gain by 10/1.5. Add better bypassing for VDDA/2 and CMOS Oscillator. Added Johnson counter. This is schematic only at the moment.
2026-05-04 Added board photo.
2026-05-04 Made cutoff about 150 kHz
2026-05-05 started routing
2026-05-05 more edits the the DAC
2026-05-05 Saved.
2026-05-05 Saved schematic
2026-05-05 edits
2026-05-05 Added CJC5340
2026-05-05 More edits....
2026-05-05 Placed the second ADC
2026-05-06 More routing
2026-05-06 Fixing unconnected
2026-05-06 Fixing errors 16 unconnected, 24 violations
2026-05-06 Finally 0 errors
2026-05-06 Silkscreen tweaks
2026-05-06 Jumper text on the back.
2026-05-06 Fixing jumper labels and missing wire
2026-05-06 Add Johnson counter MODE support to quisk_conf_2026 and widgets
2026-05-06 Fixed sub-schematic versions
2026-05-06 Jumper Labels
2026-05-06 3D Model of LEDs
2026-05-07 Changed push pull to PAM8908
2026-05-07 Saved old simulations.
2026-05-07 fixing labels 0errors
2026-05-07 I->ADC Label
2026-05-07 Label Tweaks
2026-05-07 Tweaks
2026-05-07 Yet more label tweaks
2026-05-07 H IN < 7V
2026-05-07 H-IN on 4.7 V
2026-05-07 Fixed CJC5340 C Number
2026-05-08 Input circuit for the CJT5340
2026-05-08 R43 and R44 to 100 Ohms
2026-05-08 3D model of the 40 pin connectors.
2026-05-26 Funny thing, SCXI1 and SCKI2 are mixed up, PCB vs Schematic
2026-06-07 Add Soapy-For-2026-Board module
2026-06-11 Emergency save - all files are safe
2026-06-11 Stop tracking embedded .history folder
